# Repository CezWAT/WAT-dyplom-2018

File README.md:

# WAT-dyplom-2018

Repozytorium kodu do pracy magisterskiej pt. Zdalny monitoring stanu baterii akumulatorów w pojazdach samochodowych wykonanej na Wojskowej Akademii Technicznej.

Źródło pracy Zdalny monitoring stanu baterii akumulatorów w pojazdach samochodowych

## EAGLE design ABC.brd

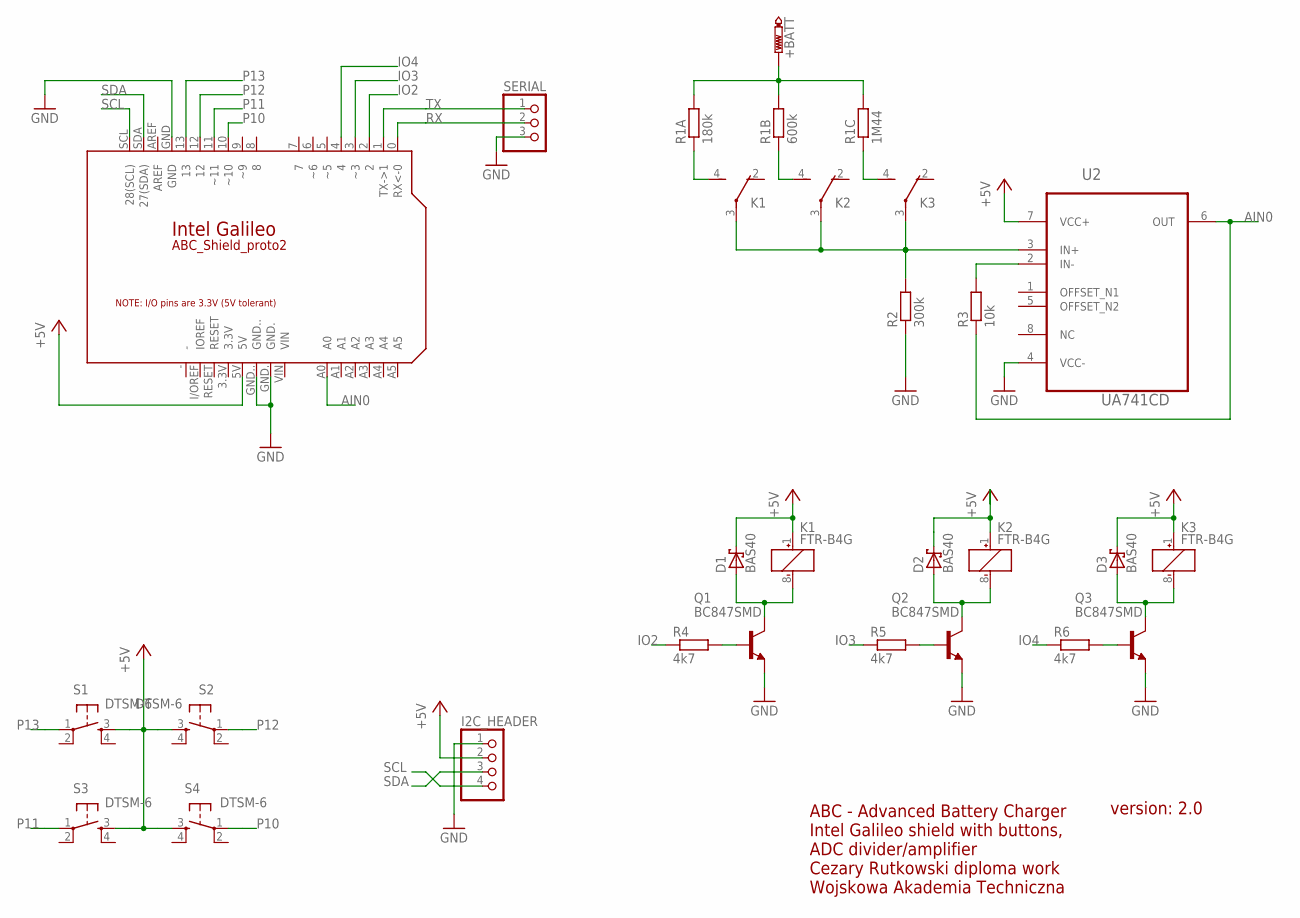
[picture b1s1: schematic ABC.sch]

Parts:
+BATT: PTR1PAD1-20Y; P1-20Y
D1, D2, D3: BAS40; SOT23
I2C_HEADER: PINHD-1X4; 1X04
K1, K2, K3: FTR-B4G
PCB1: ARDUINO_101; ARDUINO_GALILEO
Q1, Q2, Q3: BC847SMD; SOT23
R1A: 180k; M1206
R1B: 600k; M1206
R1C: 1M44; M1206
R2: 300k; M1206
R3: 10k; M1206
R4, R5, R6: 4k7; M1206
S1, S2, S3, S4: DTSM-6
SERIAL: PINHD-1X3; 1X03
U2: UA741CD; SOIC127P600X175-8N

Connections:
+5V: D1.3 (C), D2.3 (C), D3.3 (C), I2C_HEADER.2, K1.1 (+), K2.1 (+), K3.1 (+), PCB1.5V, S1.3, S2.3, S3.3, S4.3, U2.7 (VCC+)
AIN0: PCB1.A0, R3.1, U2.6 (OUT)
DIV: K1.3, K2.3, K3.3, R2.2, U2.3 (IN+)
GND: I2C_HEADER.1, PCB1.GND, PCB1.GND., PCB1.GND.., Q1.2 (E), Q2.2 (E), Q3.2 (E), R2.1, SERIAL.3, U2.4 (VCC-)
IO2: PCB1.2, R4.1
IO3: PCB1.3 (~3), R5.1
IO4: PCB1.4, R6.1
unnamed: R3.2, U2.2 (IN-)
unnamed: K1.4 (S), R1A.1
unnamed: +BATT.TP, R1A.2, R1B.2, R1C.2
unnamed: K2.4 (S), R1B.1
unnamed: K3.4 (S), R1C.1
unnamed: Q1.1 (B), R4.2
unnamed: D1.1 (A), K1.8 (-), Q1.3 (C)
unnamed: Q2.1 (B), R5.2
unnamed: D2.1 (A), K2.8 (-), Q2.3 (C)
unnamed: Q3.1 (B), R6.2
unnamed: D3.1 (A), K3.8 (-), Q3.3 (C)
P10: PCB1.10 (~10), S4.1
P11: PCB1.11 (~11), S3.1
P12: PCB1.12, S2.1
P13: PCB1.13, S1.1
RX: PCB1.0 (RX<-0), SERIAL.2
SCL: I2C_HEADER.4, PCB1.SCL (28(SCL))
SDA: I2C_HEADER.3, PCB1.SDA (27(SDA))
TX: PCB1.1 (TX->1), SERIAL.1

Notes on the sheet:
ABC_Shield_proto2
ABC - Advanced Battery Charger Intel Galileo shield with buttons, ADC divider/amplifier Cezary Rutkowski diploma work Wojskowa Akademia Techniczna
version: 2.0

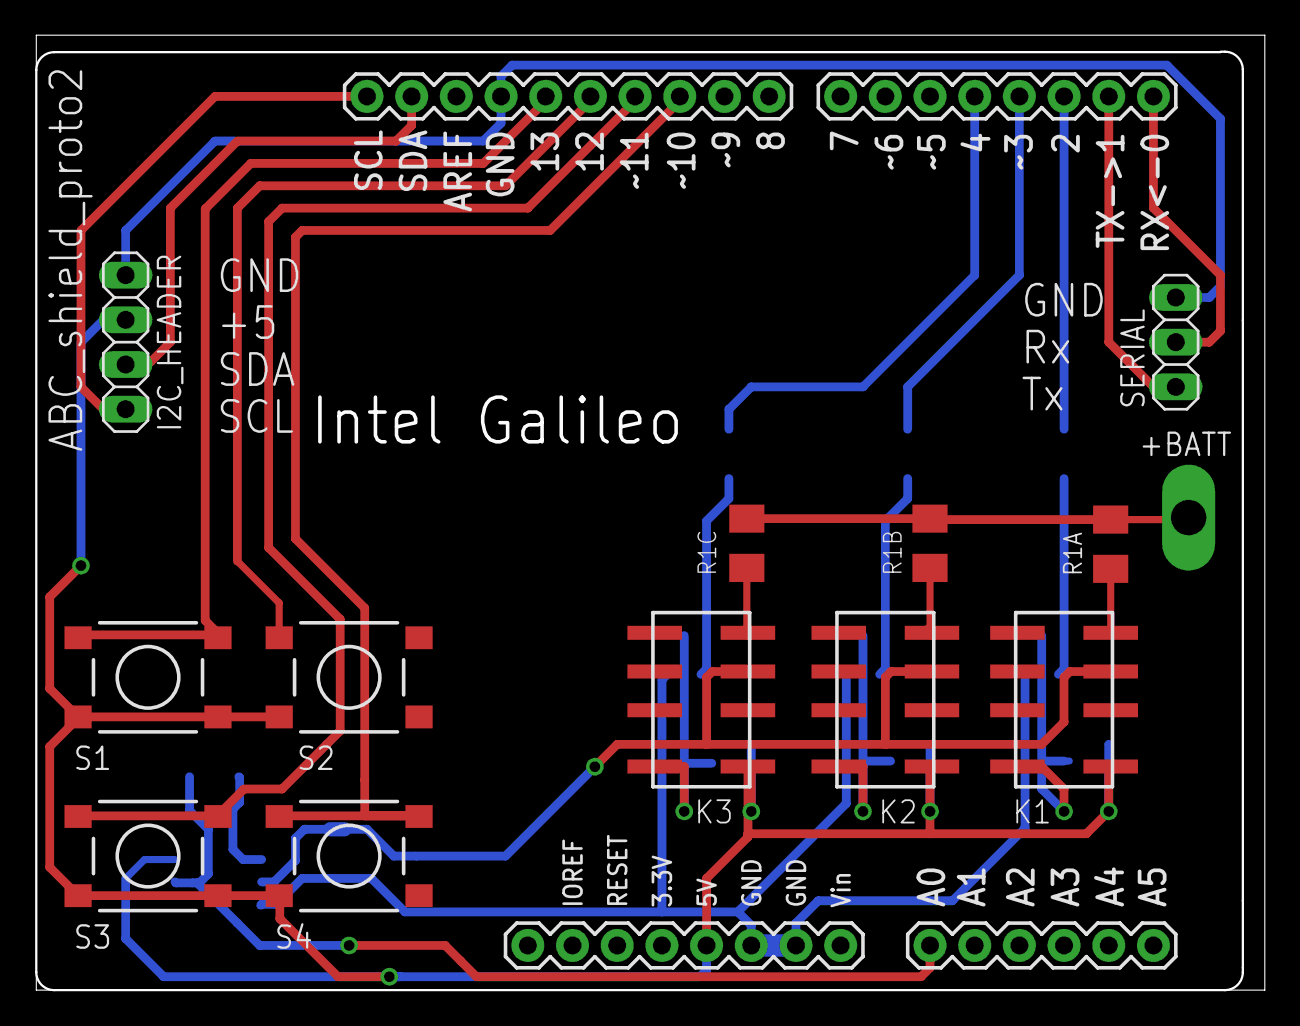
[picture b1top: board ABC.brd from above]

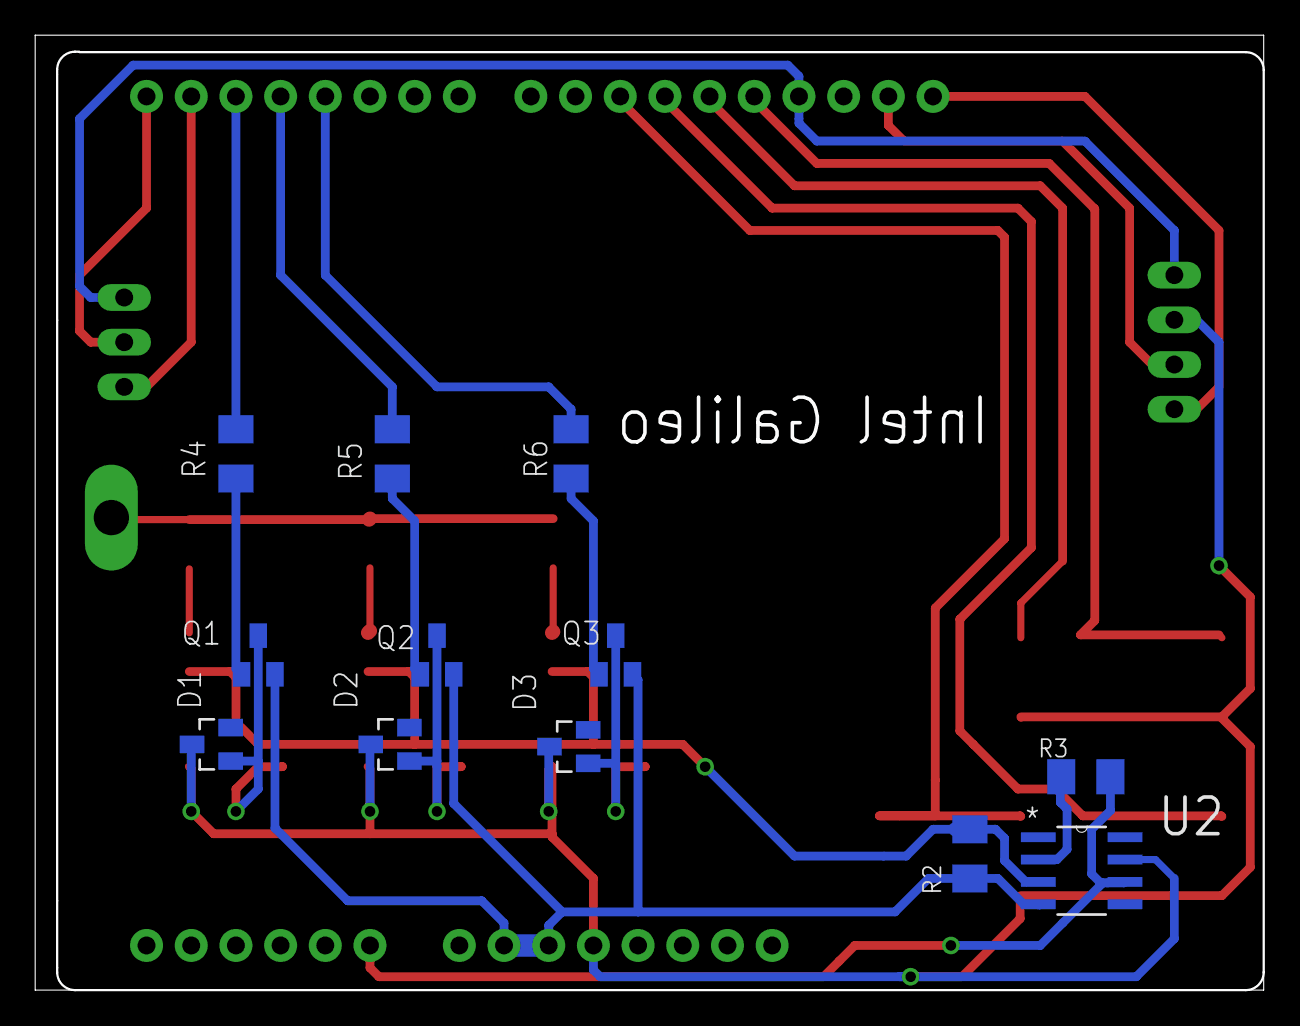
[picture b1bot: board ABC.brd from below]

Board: 2 copper layers, 69.8 x 54.3 mm, 26 parts (12 on the bottom side), 26 nets.

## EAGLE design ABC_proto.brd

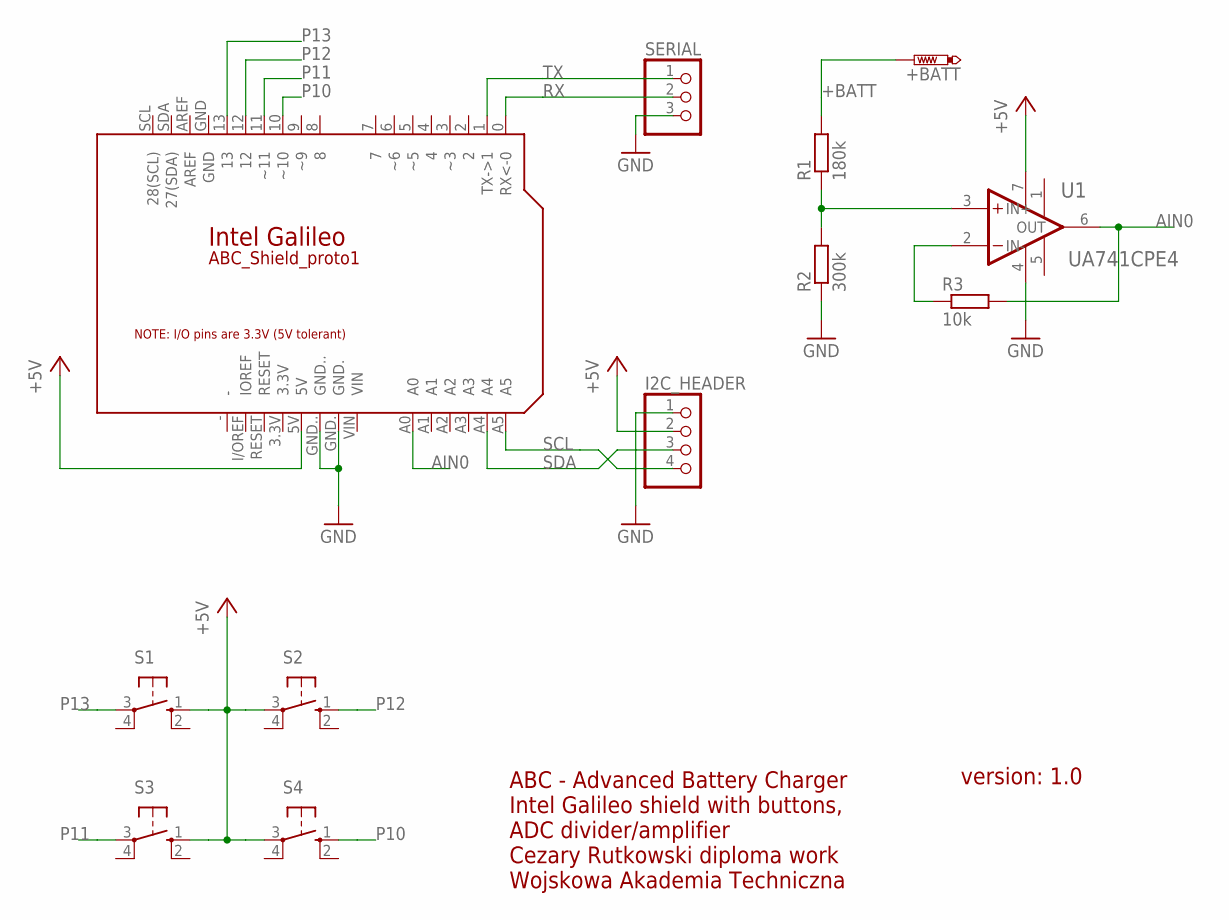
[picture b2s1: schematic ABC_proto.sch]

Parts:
+BATT: PTR1PAD1-20Y; P1-20Y
I2C_HEADER: PINHD-1X4; 1X04
PCB1: ARDUINO_101; ARDUINO_GALILEO
R1: 180k; 0204/5
R2: 300k; 0204/5
R3: 10k; 0204/5
S1, S2, S3, S4: 10-XX; B3F-10XX
SERIAL: PINHD-1X3; 1X03
U1: UA741CPE4; DIP254P762X508-8

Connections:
+5V: I2C_HEADER.2, PCB1.5V, S1.1 (S), S2.3, S3.1 (S), S4.3, U1.7 (VCC+)
+BATT: +BATT.TP, R1.2
AIN0: PCB1.A0, R3.2, U1.6 (OUT)
DIV: R1.1, R2.2, U1.3 (IN+)
GND: I2C_HEADER.1, PCB1.GND., PCB1.GND.., R2.1, SERIAL.3, U1.4 (VCC-)
unnamed: R3.1, U1.2 (IN-)
P10: PCB1.10 (~10), S4.1 (S)
P11: PCB1.11 (~11), S3.3
P12: PCB1.12, S2.1 (S)
P13: PCB1.13, S1.3
RX: PCB1.0 (RX<-0), SERIAL.2
SCL: I2C_HEADER.4, PCB1.A5
SDA: I2C_HEADER.3, PCB1.A4
TX: PCB1.1 (TX->1), SERIAL.1

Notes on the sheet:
ABC_Shield_proto1
ABC - Advanced Battery Charger Intel Galileo shield with buttons, ADC divider/amplifier Cezary Rutkowski diploma work Wojskowa Akademia Techniczna
version: 1.0

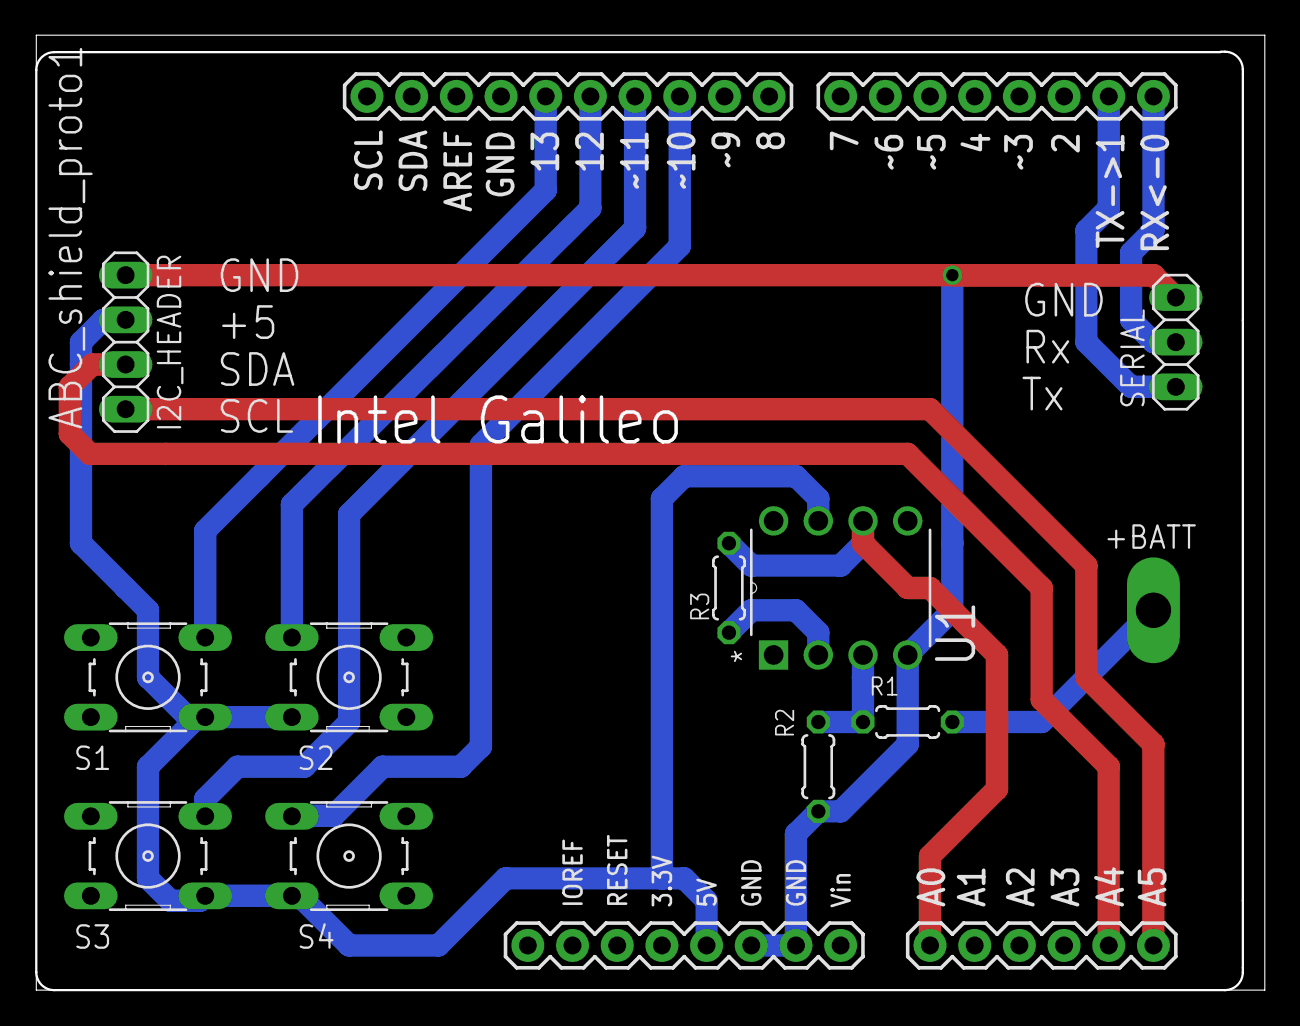
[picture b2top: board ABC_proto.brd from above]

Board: 2 copper layers, 69.8 x 54.3 mm, 12 parts (0 on the bottom side), 14 nets.

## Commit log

2019-01-13 Revert "Initial commit"
    This reverts commit 495110ab46150307beb918f90b46196368a5e4cd.
2019-01-13 Revert "Revert "Initial commit""
    This reverts commit d39897e480ad33b1cac9b1d8c5c07198d602a23b.
